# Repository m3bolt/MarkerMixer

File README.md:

<!-- PROJECT LOGO -->
<br />
<p align="center">

  <p align="center">
   Marker mixer/blender for dying filament with permanent markers before it enters the hotend
    <br />
	<a href="https://discord.gg/TchtRx5vXf"><strong>Join the PMP Discord </strong></a>
	·
    <a href="https://github.com/m3bolt/MarkerMixer/tree/main/STLs"><strong>Download STLs </strong></a>
	·
    <a href="https://www.youtube.com/watch?v=Sshl-3-f8Ro"><strong>PMP Demo Video </strong></a>
    ·
    <a href="https://github.com/m3bolt/MarkerMixer/issues">Report Bug</a>
    ·
    <a href="https://github.com/m3bolt/MarkerMixer/issues">Request Feature</a>
  </p>
</p>

<!-- ABOUT THE PROJECT -->
## About The Project

The Poor Mans Palette is designed to use servos to slide markers in out and of a central filament path. It is an evolution of and directly inspired by Youtuber Makers Muse who designed a manual version.

<!-- GETTING STARTED -->
## Getting Started

Using the Poor Mans Palette is easy, but it does require some setup. <a href="https://github.com/kackle1998">Viperian</a> has created <a href="https://docs.google.com/document/d/1HtXDXiIX8TrwlF5AgzMKKhFVkw75yK6E26BhG-3SkN0/edit"><strong>Google Doc Instructions</strong></a> for new users to set up and use their PMP. 

You will need some electronics and hardware:

| Part Name | Description | Quantity |
| ------------- | ------------- | ------------- |
| 3D Printer running Klipper | Klipper is required for servo control | 1 |
| Arduino (Nano or Uno)  | Used by Klipper to address servo pins  | 1 |
| 5v 1A+ Power Supply | Necessary to power servos, barrel jack recommended | 1 |
| M3 x 10mm screw | To secure Marker Holder to Marker Hub | 6 |
| M3 x 12mm screw | To hold the marker in in the Marker Slider | 3 |
| M3 Locknut | To secure Marker Screw Cap to 12mm screw | 3 | 
| M3 x 16mm screw | To mount Marker Hub to your printers Hub Mount | 3 |
| Breadboard or Perfboard | Used for wiring servos to the Arduino | 1 |
| 3-pin DUPONT headers | For plugging the servos into your breadboard or perfboard | 3 |
| SG90 Servo Motor | Used to extend and retract the markers | 3 |
| SG90 Servo mounting screws | Usually included with your SG90, these secure the servo to the Marker Body | 6 |

The following are the STLs required for a 3 marker setup and the quantity of each required: 

| Part Name | Notes | Quantity |
| ------------- | ------------- | ------------- |
| PMP_MarkerHub_R1.stl | | 1 |
| PMP_MarkerBody_NumX_R1.stl | Requires supports! Print NoNum for no numbers or 1-3 for numbered versions. | 3 |
| PMP_MarkerSlider_Size_ID_R1.stl | 2 versions available, one with a smaller ID and one with a larger ID. Print one at a time to verify the size required! | 3 |
| PMP_ServoGear_Size_ID_R1.stl | 5 versions available with different IDs for the servo shaft. Print one at a time to verify the size required! | 3 |
| PMP_MarkerScrewCap_R1.stl | Optional thumb screw caps for the set screw holding the marker in the slider | 3 |

Hub mounts to follow for some machines. 

In theory you can stack PMPs on top of eachother for even more color combinations and options, but we recommend starting with one set of 3. 

<!-- CONTACT -->
## Contact

If you need help or want to reach out, message Viperian and M3 Bolt on our 	<a href="https://discord.gg/TchtRx5vXf">Discord server.</a>

Project Link: https://github.com/m3bolt/MarkerMixer

<!-- LICENSE -->
## License

Distributed under the Creative Commons Attribution-NonCommercial-ShareAlike 4.0 license.

<!-- ACKNOWLEDGEMENTS -->
## Acknowledgements

* <a href="https://github.com/kackle1998">Viperian,</a> who originally had the idea of automatic slicer controlled marker switching and did all of the software/slicer parts of the project.
* <a href="https://www.youtube.com/channel/UCxQbYGpbdrh-b2ND-AfIybg">Makers Muse,</a> who showed a video of a manual marker filament dying system that inspired the project.
* <a href="https://github.com/m3bolt">M3 Bolt,</a> who did most of the Fusion based CAD work for the project.

<!-- MARKDOWN LINKS & IMAGES -->
<!-- https://www.markdownguide.org/basic-syntax/#reference-style-links -->
[contributors-shield]: https://img.shields.io/github/contributors/github_username/repo.svg?style=for-the-badge
[contributors-url]: https://github.com/github_username/repo/graphs/contributors
[forks-shield]: https://img.shields.io/github/forks/github_username/repo.svg?style=for-the-badge
[forks-url]: https://github.com/github_username/repo/network/members
[stars-shield]: https://img.shields.io/github/stars/github_username/repo.svg?style=for-the-badge
[stars-url]: https://github.com/github_username/repo/stargazers
[issues-shield]: https://img.shields.io/github/issues/github_username/repo.svg?style=for-the-badge
[issues-url]: https://github.com/github_username/repo/issues
[license-shield]: https://img.shields.io/github/license/github_username/repo.svg?style=for-the-badge
[license-url]: https://github.com/github_username/repo/blob/master/LICENSE.txt
[linkedin-shield]: https://img.shields.io/badge/-LinkedIn-black.svg?style=for-the-badge&logo=linkedin&colorB=555
[linkedin-url]: https://linkedin.com/in/github_username

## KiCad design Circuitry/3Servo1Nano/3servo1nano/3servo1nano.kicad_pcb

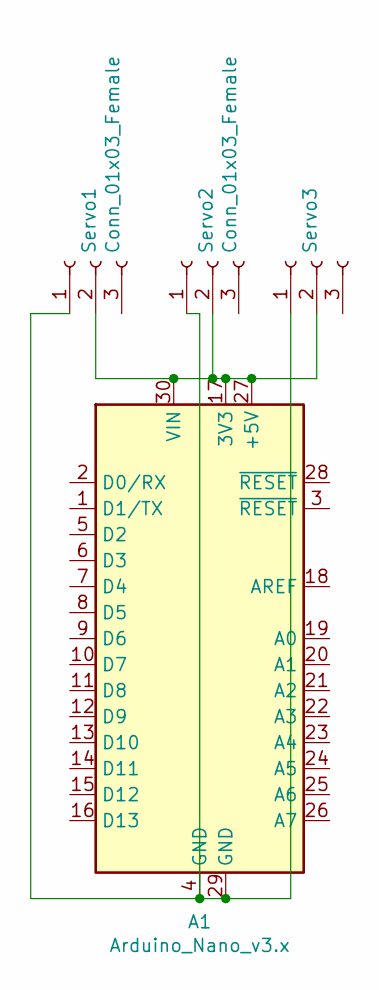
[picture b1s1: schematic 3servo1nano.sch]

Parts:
A1: Arduino_Nano_v3.x; Arduino_Nano
Servo1, Servo2, Servo3: Conn_01x03_Female; PinHeader_1x03_P2.54mm_Vertical

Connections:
unnamed: A1.17 (3V3), A1.27 (+5V), A1.30 (VIN), Servo1.2, Servo2.2, Servo3.2
unnamed: A1.4 (GND), A1.29 (GND), Servo1.1, Servo2.1, Servo3.1

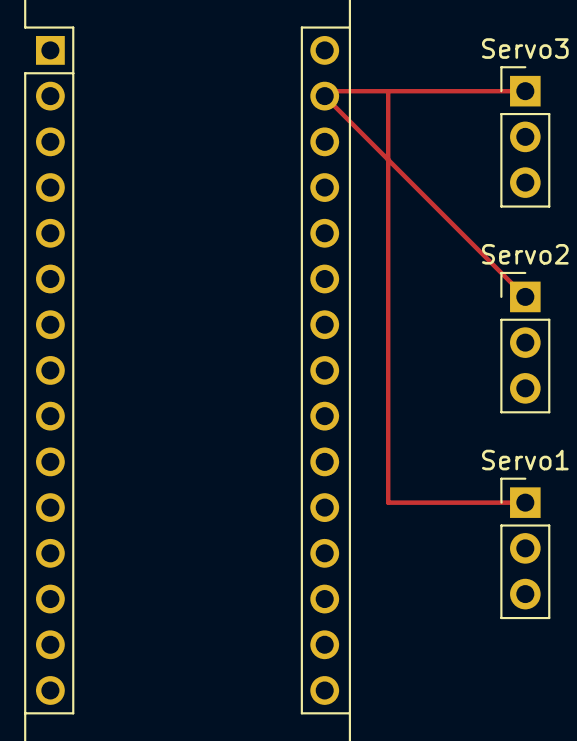
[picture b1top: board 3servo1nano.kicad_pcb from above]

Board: 2 copper layers, 4 parts (0 on the bottom side), 2 nets.

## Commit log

2021-03-13 Update README.md
    First README update
2021-03-13 v0 STLs
    v0 files
2021-03-13 v0 STLs
2021-03-13 v0 CAD assembled
2021-03-13 Messy Fusion 360
2021-03-17 Added new v1 parts
    v1 uses a rack and pinion style system for better torque.
2021-03-17 Added new v1 parts
2021-03-17 Added v1 longer slide body
2021-03-17 Code for controlling via High/Low signals
    Pins optimized for Nano wiring
2021-03-17 Messy v1 Fusion 360 File
2021-03-18 Cura_Plugins_Init
    First Draft of Cura Plugin
2021-03-18 CuraFirstFunctionalDraft
    Replace the old filamentchange script with this one. No idea why I can't make a new script
2021-03-18 High/Low pin level control file
2021-04-21 Add v0 Drop In Nut Hub
2021-04-22 FirstWorkingDraft
2021-04-22 FirstWorkingDraftFixed
2021-04-24 Tolerance adjustments to drop in nut hub
2021-04-24 v1 drop in hub added, v0 deleted
2021-04-26 WIP Test files for tolerance changes
2021-04-30 FixedCura
2021-05-13 Added solenoid files
2021-05-13 Rename README.md.txt to README.md
2021-05-13 Added solenoid version CAD picture
2021-05-15 v1 solenoid STLs
2021-05-16 AutoReplaces
2021-05-16 BetterAutoReplace
2021-05-17 Added thumb screw cap
2021-05-29 Upload PMP Release R1 files
2021-05-29 Update Readme for R1 part names
2021-05-29 Add R1 STLs
2021-05-29 Delete Circuitry/3Servo1Nano/3servo1nano directory
    No longer needed
2021-05-29 Delete Scripts/Arduino directory
    No longer used
2021-06-03 PMP Temp Logo
